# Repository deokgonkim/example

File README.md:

# example

[Google](https://www.google.com/)

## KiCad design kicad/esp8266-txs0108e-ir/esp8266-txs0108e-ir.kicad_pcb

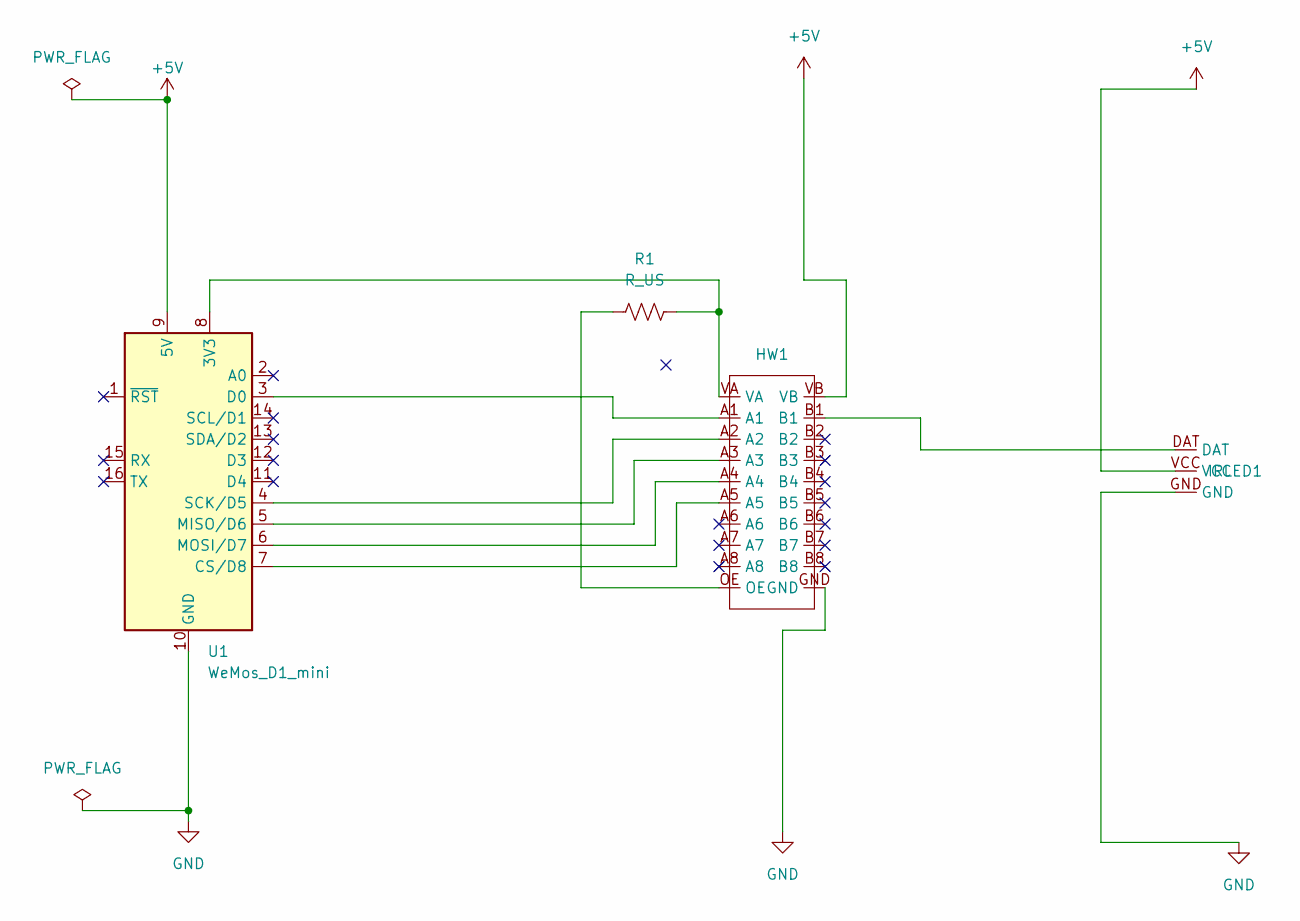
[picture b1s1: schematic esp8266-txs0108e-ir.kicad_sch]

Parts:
HW1: HW221
IRLED1: IRLED
R1: R_US; R_Axial_Power_L20.0mm_W6.4mm_P22.40mm
U1: WeMos_D1_mini; WEMOS_D1_mini_light

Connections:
+5V: HW1.VB, IRLED1.VCC, U1.9 (5V)
GND: HW1.GND, IRLED1.GND, U1.10 (GND)
unnamed: HW1.B1, IRLED1.DAT
unnamed: HW1.OE, R1.1
unnamed: HW1.VA, R1.2, U1.8 (3V3)
unnamed: HW1.A5, U1.7 (CS/D8)
unnamed: HW1.A1, U1.3 (D0)
unnamed: HW1.A3, U1.5 (MISO/D6)
unnamed: HW1.A4, U1.6 (MOSI/D7)
unnamed: HW1.A2, U1.4 (SCK/D5)

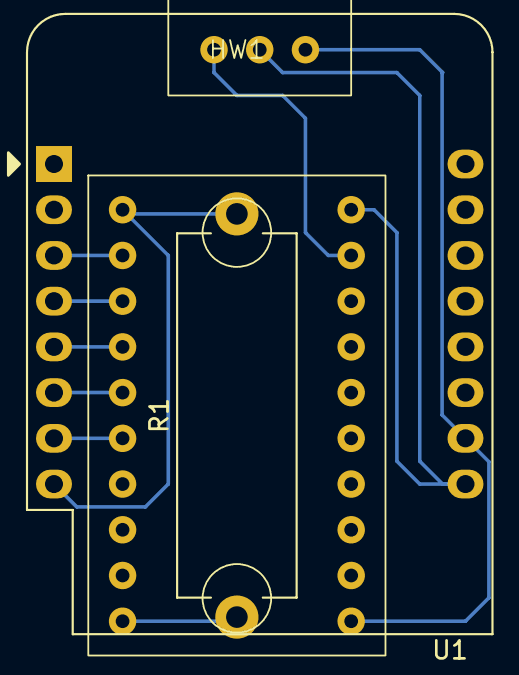
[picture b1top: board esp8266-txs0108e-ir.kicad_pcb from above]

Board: 2 copper layers, 4 parts (0 on the bottom side), 10 nets.

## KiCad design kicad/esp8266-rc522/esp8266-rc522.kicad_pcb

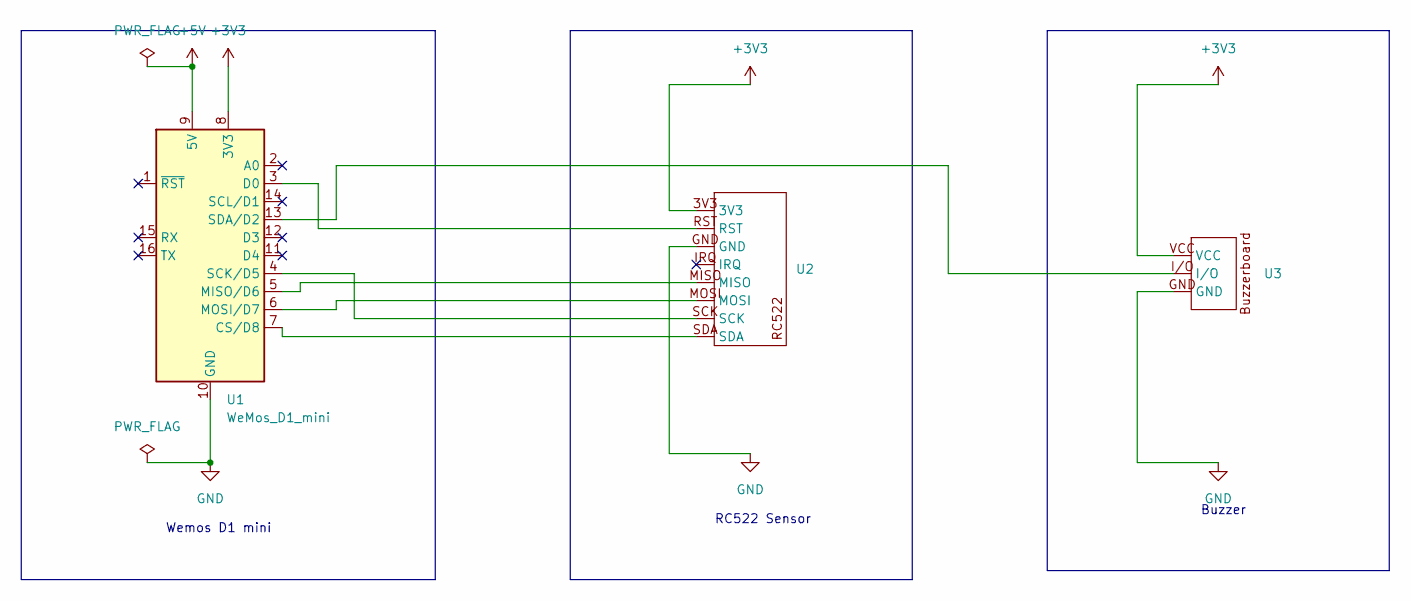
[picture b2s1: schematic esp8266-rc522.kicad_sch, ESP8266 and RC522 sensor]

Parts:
U1: WeMos_D1_mini; WEMOS_D1_mini_light
U2: RC522
U3: BuzzerBoard

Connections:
+3V3: U1.8 (3V3), U2.3V3, U3.VCC
+5V: U1.9 (5V)
GND: U1.10 (GND), U2.GND, U3.GND
unnamed: U1.7 (CS/D8), U2.SDA
unnamed: U1.3 (D0), U2.RST
unnamed: U1.5 (MISO/D6), U2.MISO
unnamed: U1.6 (MOSI/D7), U2.MOSI
unnamed: U1.4 (SCK/D5), U2.SCK
unnamed: U1.13 (SDA/D2), U3.I/O

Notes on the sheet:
Buzzer
RC522 Sensor
Wemos D1 mini

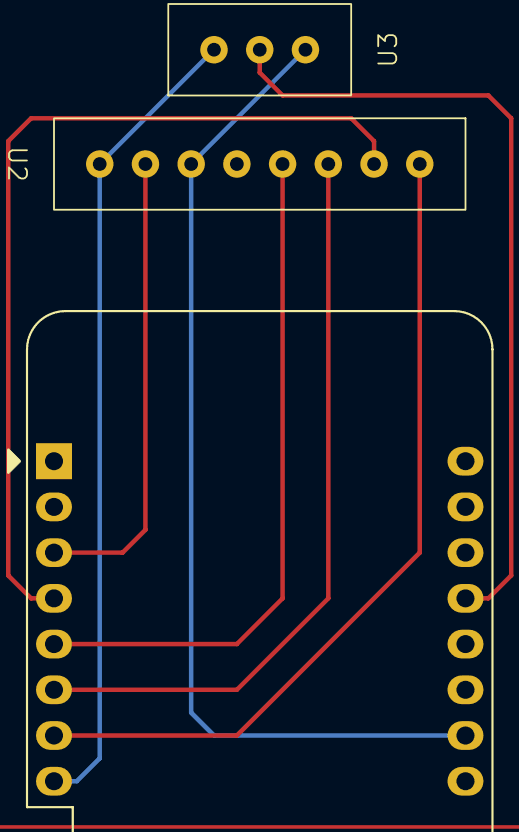
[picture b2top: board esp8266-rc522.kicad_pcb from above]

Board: 2 copper layers, 3 parts (0 on the bottom side), 8 nets.

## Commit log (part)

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2022-08-31 trangular?..
2022-09-01 tested docker node
2022-09-02 add serverless/sqs-partial-failure
2022-09-02 add cloudformation/ecs-deployment
2022-09-06 add elasticapm-lxc
2022-09-07 update elasticapm-lxc
2022-09-20 add common.util.chunk
2022-09-21 add aws secrets-manager script
2022-09-27 add javascript google sheets example
2022-09-27 add .env.example
2022-10-12 add nodejs-cli-prompt example
2022-10-20 add weblogic admin server start script
2022-10-20 add java/maven
2022-10-23 add tex helloworld example
2022-10-23 add classic asp sha256
2022-10-23 add vbs/sayit
2022-10-24 add some wakeonlan script
2022-10-25 add shell scripts
2022-10-25 add cors test script
2022-10-25 add iptables ebtables example
2022-10-27 add socket-io-redis sample
2022-11-10 tested azure container
2022-11-18 add locust sample
2022-11-24 add helloworld julia
2023-01-25 add ip.vbs
2023-01-30 add docker-clean.sh
2023-01-30 add xcode/del-unused-coresimulator.sh
2023-01-30 add apple
2023-01-30 add docker scripts
2023-01-30 add draw-io/draw_points.py
2023-01-30 add aws allow-google-security
2023-01-30 add apple local-route.sh
2023-05-10 fix image resizer bucket name pattern
2023-05-18 add esphome example
2023-05-18 add reference document
2023-05-21 add ds18b20, switch on esphome
2023-05-22 setup pir sensor, remove bmp180 sensor
2023-06-15 add livingroom2
2023-06-21 add esp8266/micropython
2023-06-21 add openai helloworld
2023-06-21 tested completion
2023-06-23 add esp8266/nodemcu
2023-06-26 add nodejs/password.js
2023-06-26 add aws/vpc-delete.sh
2023-07-09 add esphome/livingroom
2023-07-25 add esphome/esp32cam
2023-07-25 update esphome/esp32cam
2023-08-12 remove pirsensor from livingroom.yaml
2023-09-08 add gcp
2023-09-08 add serverless/gcp-hello
2023-09-08 update serverless/gcp-hello
2023-11-15 add esphome/livingroom4
2023-12-25 update lambda node runtime
2023-12-28 update livingroom4
2024-01-01 update serverless/image-resizer
2024-01-01 fix image resizer
2024-02-20 tested child directory
2024-02-20 add nodejs/module/ts-consumer
2024-02-28 python image manipulation 누끼
2024-03-05 add serverless-docker-sample
2024-03-05 add example lambda nest entrypoint
2024-03-07 tested qr-image
2024-05-16 tested tensorflow lite image classification
2024-05-20 add electron/helloworld
2024-05-23 add dockerizing file to image_classification
2024-05-28 tested openai node chat completion
2024-05-28 tested openai api with intend detection
2024-05-28 fix unavailable timeslot
2024-06-08 update esphome
2024-06-08 add esphome/aircon
2024-06-10 add react/test-router-and-history
2024-06-11 first langchain
2024-06-12 test langchain/rag_first
2024-06-13 add streamlit/helloworld
2024-06-13 tested langchain/tool_chain
2024-06-13 comment unused code
2024-06-13 add launch configuration for tool_chain/dayplanner
2024-06-14 add huggingface/diffusion
2024-06-17 add python/ocr
2024-06-19 add ios/app-intent
2024-06-26 add helloworld/kivy
2024-06-26 add helloworld/tkinter
2024-07-03 add telegram/first
2024-07-04 tested list channel
2024-07-11 tested slack dialog
2024-07-12 add esphome/rc522
2024-07-16 update esphome/aircon
2024-07-21 add esphome/pn532
2024-07-23 upgrade esphome/rc522
2024-08-09 add shell-scripts/notify_me.sh
2024-08-10 update esphome/pn532
2024-08-13 add elasticapm/script
2024-08-23 add git/get_current_version.sh
2024-08-23 update git/get_current_version
2024-08-25 add freecad/first-model
2024-08-26 update freecad/esp8266-pn532
2024-08-26 update esp8266-pn532-v6
2024-08-26 add freecad/esp8266-pn532/esp8266-pn532.drawio
2024-08-27 update freecad/esp2826-pn532
2024-08-29 add kicad/first output files
2024-08-29 add kicad/first image
2024-08-29 update kicad/first
2024-08-29 add kicad/esp8266-rc522
2024-08-31 update freecad/ir-transceiver
2024-08-31 add freecad/lolind1minipro
2024-09-02 add freecad/ir-bracket
2024-09-03 add freecad/rpi4-bracket
2024-09-08 add freecad/pir-sensor/draft.txt
2024-09-12 add freecad/block
2024-09-13 add freecad/heat-gun-holder
2024-09-14 add freecad/rope-guide
2024-09-20 add freecad/hanger-gap
2024-09-20 add kicad/esp8266-txs0108e-ir
2024-09-21 add freecad/aircon-esp8266-ir
2024-09-22 add freecad/cable-reel
2024-09-28 add freecad/d1mini-case
2024-09-28 update feecad/d1mini-case
2024-09-28 add freecad/esp32cam-case
2024-10-01 add freecad/hand-drill-addon
2024-10-03 add freecad/tape-holder
2024-10-06 update freecad/tape-holder
2024-10-08 tested reportlab
2024-10-10 tested nodejs/pdf-lib-test
2024-10-14 add shellscript disable-super-period
2024-10-18 add escpos/test
2024-10-20 update esphome/rc522
2024-10-20 add freecad/rc522-d1-mini
2024-10-21 tested escpos python
2024-11-01 add freecad/piston-for-cleanser
2024-11-03 add freecad/tissue-holder
2024-11-03 add freecad/razor-blade-storage
2024-11-05 initial commit for telegram/serverless-telegram-bot
2024-11-05 wip: serverless-telegram-bot
2024-11-06 implement serverless-telegram-bot
2024-11-06 update serverless-telegram-bot
2024-11-06 update cognito/rect-cognito-client - implement return page and oauth authorization flow
2024-11-07 feat: tested twilio whatsapp api
2024-11-14 add serverless/websocket-test
2024-11-23 add freecad/clothes-hanger-ring
2024-12-04 add freecad/card-holder
2024-12-16 add gnome/gjs, gnome/pygobject
2024-12-17 add freecad/hanger-coupler
2024-12-18 add arduino/hello-world
2024-12-18 update arduino/goodisplay_097
2024-12-18 wip google-chat/send-message
2024-12-19 tested google-chat/send-message
2024-12-23 add flatpak/hello
2024-12-23 update gnome/gjs/hello-gnome-builder
2024-12-23 add snap/first
2024-12-23 fix: snap command to be included
2025-01-02 tested grpc
2025-01-08 tested openai streaming api
2025-01-08 tested openai completion with streaming
2025-01-08 add freecad/plastic-cap
2025-01-11 add freecad/propeller-guard
2025-01-14 tested nestjs-swagger
2025-01-16 add micropython/m5nanoc6
2025-01-16 print when button is pressed
2025-02-12 add apps-script
2025-02-12 add golang/gin-with-apm
2025-02-14 add gnome/gnome-extensions
2025-02-14 add freecad/piston-for-toothpaste
2025-02-17 update gnome-extensions/dgkim-first
2025-02-19 dd swift/swift-cli
2025-02-19 update swift/swift-playground
2025-02-19 update swiftui-webview
2025-02-19 add mysql_lock_check
2025-02-22 add piston-for-toothpaste-28mm
2025-02-24 add backup-to-s3
2025-02-25 add cleaning-up-old-xcode-files.txt
2025-02-26 add helloworld/rust-druid
2025-02-26 tested gjs fetch data over http
2025-02-26 tested gjs/hello-gnome-builder - tested ui handling - tested data fetching on gjs - tested event handling on ui
2025-02-27 add docker/webtop
2025-03-04 fix: swift ui webview
2025-03-04 feat: make webview inspectable
2025-03-05 tested gnome/gjs/dbus-test
2025-03-05 tested gnome dbus and notification
2025-03-10 doc: update changelog
2025-03-13 add freecad/piston-for-cleanser/piston-for-toothpaste-35_5mm
2025-03-13 update hanger-coupler
2025-03-13 add freecad/a4-half
2025-03-17 add freecad/piston-for-cleanser/piston-for-toothpaste-34mm
2025-03-17 update piston-for-toothpaste-34mm
2025-03-19 add arduino/pn532_url
2025-03-20 add storybook/component-installable
2025-03-20 add storybook/component-installable-consumer
2025-03-20 add storybook
2025-03-20 add npm/create-app
2025-03-23 update freecad/block
2025-04-01 update freecad/hanger-coupler
2025-04-07 add chrome-extension/wanted-filter-extension
2025-04-07 feat: [wanted-filter-extension] support jumpit
2025-04-07 add mcp/first
2025-04-08 update chrome-extension/wanted-filter-extension
    - feat: implement download as json to backup the list
2025-04-10 udpate chome-extension/wanted-filter-extension
2025-04-11 update chrome-extension/wanted-filter-extension
    - feat: support rocketpunch
2025-04-11 add firefox-extension/wanted-filter-extension
2025-04-15 update freecad/a4-half
2025-04-17 tested openai/codex
2025-04-25 add freecad/jinhao-x159-piston-handle
2025-04-25 add freecad/fountainpen-holder-thicker
2025-05-03 update freecad/fountainpen-holder/sheet
2025-05-06 update freecad/fountainpen-holder-thicker
2025-05-13 add freecad/plastic-cap/platic-cap-with-screw
2025-05-15 add apple/coreml/first-coreml
2025-05-19 add web3/first-node
2025-05-24 add freecad/rpi3-cam-holder
2025-05-24 update freecad/rpi3-cam-holder
2025-05-25 update freecad/piston-for-cleanser
2025-05-29 add youtube/mysubscriptions
2025-05-29 add freecad/funnel
2025-05-31 update huggingface/diffusion
2025-05-31 update freecad/funnel
2025-06-01 add freecad/door-hanger/door-hanger-mini
2025-06-17 add freecad/inking-cup
2025-06-29 add freecad/fan-duct
2025-07-04 add freecad/coffee-bag-funnel
2025-07-09 add freecad/hook
2025-07-09 add freecad/stopper/stopper-arc
2025-07-12 add freecad/cable-holder/cable-holder-with-magnet
2025-07-13 update freecad/fountainpen-holder-v2
2025-07-16 add freecad/baseus65w-hook
2025-07-16 add freecad/hook/hook-cookware
2025-07-17 add freecad/hook/hook-longnose
2025-07-18 update freecad/hook/hook-longnose
2025-07-21 add freecad/hook/hook-for-pole
2025-07-21 add freecad/hook/hook-for-wineopener
2025-08-01 add freecad/hook/hook-for-belt
2025-08-01 add freecad/hook/hook-for-belt-v2
2025-08-05 add freecad/funnel/funnel-46mm-86mm
2025-08-05 add freecad/fountainpen-holder/v2/open-cap-platinum-starlet-small-hole
2025-08-10 add freecad/funnel/funnel-20mm-80mm
2025-08-13 add freecad/hook/hook-for-spoon, freecad/hook/hook-m-shape
2025-08-20 add freecad/hook/hook-cookware-5mm-v2
2025-08-23 add freecad/magazine/hexagon-20mm
2025-08-31 add freecad/case-postit
2025-09-14 update freecad/hook
2025-09-19 tested react/first-tailwind
2025-09-23 add react/first-shadcn
2025-10-08 add freecad/razor-blade-storage/razor-blade-storage-v2
2025-10-31 add freecad/hook/hanger-for-belt
2025-11-09 migrated to another repository
2025-12-10 add escpos/test/pyinstaller.md
2025-12-10 add langchain/first/sd
2025-12-10 add nodejs/node-escpos-test
2025-12-14 add conky/first.conkyrc
2025-12-14 add conky/conkyrc-for-syuka
2025-12-15 update gcp/README.md
    Add instructions for copying files from Firebase storage to local.
2025-12-28 remove gcode file
2025-12-31 update flask/local-webserver - add requirements
2026-01-02 add aws/nested-stack
2026-01-07 move go example to cli
2026-01-07 add helloworld/go/rest-api sample
2026-01-09 fix: youtube/channel-logos not to contain inappropriate result
2026-01-11 add nosleep
2026-01-11 update talk
2026-01-18 add python/convert-sharex-to-bsky
2026-01-23 update python/image-by-year
2026-01-23 add shell-scripts/dedupe_sha1.sh
2026-02-14 add vbs/detect.vbs
2026-03-02 add conversation with codex
2026-03-03 add python/photo
2026-03-03 add python/photo/generate_camera_geojson.py
2026-03-03 add option to include href for the file in python/photo/generate_camera_geojson.py
2026-03-04 add python/dash-treemap
2026-03-04 update python/dash-treemap
2026-03-04 add python/dash-treemap/sample.png
2026-03-05 add youtube/mysubscriptions/watch_history_marketcap_treemap_plotly.py
2026-03-05 add shell-scripts/ubuntu/find-installed-via-ppa.sh
2026-03-05 update conky sample configs
2026-03-06 add python/firefox/firefox-bookmark-differ
2026-03-12 add helloworld/tauri
2026-03-12 add ai-agent
2026-03-13 add serverless/rmovie
2026-03-14 feat: update serverless/rmovie
    - Use crypto.randomInt for random row selection
2026-03-15 chore: update serverless/rmovie
    - chore: update lambda runtime from node20 to node20
2026-03-19 add shell-scripts/usbmux.sh
2026-03-21 add youtube/youtube-video-export-devtools
2026-03-21 update youtube/youtube-video-export-devtools
2026-03-21 update youtube/youtube-vide-export-devtools
2026-03-24 add shell-scripts/macos/disable_dsstore_network.sh
2026-03-26 add shell-scripts/ubuntu/tap-and-drag.sh
2026-03-26 add shell-scripts/ubuntu/natural-scroll
2026-03-26 add shell-scripts/ubuntu/ibus.sh
2026-03-29 add apache/ip
2026-03-29 add shell-scripts/ubuntu/disable-ipv6.sh
2026-03-30 add shell-scripts/home-assistant
2026-03-30 add shell-scripts/ubuntu/noti_slack.sh
2026-04-01 add ffmpeg/heic2jpg.sh
2026-04-01 add ffmpeg/heic2jpg_v2.sh
2026-04-01 update serverless/rmovie
2026-04-02 add x509/simplest-web-ca
2026-04-03 update slack/mail-like-tui
    - support block and attachments
2026-04-03 update slack/mail-like-tui
    - implement user ability to switch channel
2026-04-03 update slack/mail-like-tui
    - [changelog/responsive-layout-and-fullscreen-picker.md]
2026-04-10 add ffmpeg/frame-count.sh
2026-04-15 add helloworld/aws-eks-kotlin
2026-05-05 add keycloak/helloworld
2026-05-05 add diagrams
